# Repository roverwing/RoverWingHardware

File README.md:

Introduction
============
RoverWing is an extension board  (or "wing", following Adafruit's terminology) for Adafruit's [Feather boards](https://www.adafruit.com/feather).
This board  provides motor drivers, Inertial Motion Unit (IMU), and connection ports for servos, sonars, GPS,
and other peripherals commonly used by mobile robots. It also contains a microcontroller preloaded with firmware
to control these peripherals, which communicates with the Feather board using I2C protocol, thus freeing resources
of the Feather board for other purposes.

The RoverWing was heavily influenced by Adafruit's [CRICKIT](https://www.adafruit.com/crickit) board
(in particular, it has exact same dimensions and  mounting holes as the CRICKIT board). However, unlike CRICKIT,
it is intended for use with more powerful 6-12V motors and provides a slightly different set of peripherals.

Below is the list of key features of the RoverWing:

* Can be powered by 7-14V power source; contains a voltage regulator providing power to the Feather board

* Only uses 2 pins (SDA and SCL) of the Feather board.

* Contains on-board microcontroller, which takes care of low-level operations such as counting motor encoder pulses, using preloaded firmware

* Contains on-board 6DOF  Inertial Motion Unit (IMU),  based on ICM-42605 chip
  by Invensense, which can be used for tracking robot orientation in space

* Provides the hardware and firmware support for connecting the following external peripherals

  - Motors: two brushed DC motors, at up to 2.9A at 14V per motor
  - Quadrature encoders for each motor
  - Sonars: support for three HC-SR04 or compatible ultrasonic sensors (sonars)
  - Servos: four servos (5V)
  - Six analog inputs (3.3V)
  - NeoPixel smart LED (see note on power limit below)
  - GPS  sensor
  - one  additional I2C device

The RoverWing uses same connectors for power supply, motors, encoders, and I2C
sensors as the [REV Robotics Expansion hub](http://www.revrobotics.com/rev-31-1153)  used in [First Tech Challenge](https://www.firstinspires.org/robotics/ftc)  robotics competition, so it can
be easily used with the same motors and sensors.

   RoverWing (without the Feather), top view.

For complete documentation of RoverWing board, please visit https://roverwing-board.readthedocs.io/.

To use RoverWing board, you need to install [RoverWing library for Arduino](https://github.com/roverwing/RoverWingLibrary).

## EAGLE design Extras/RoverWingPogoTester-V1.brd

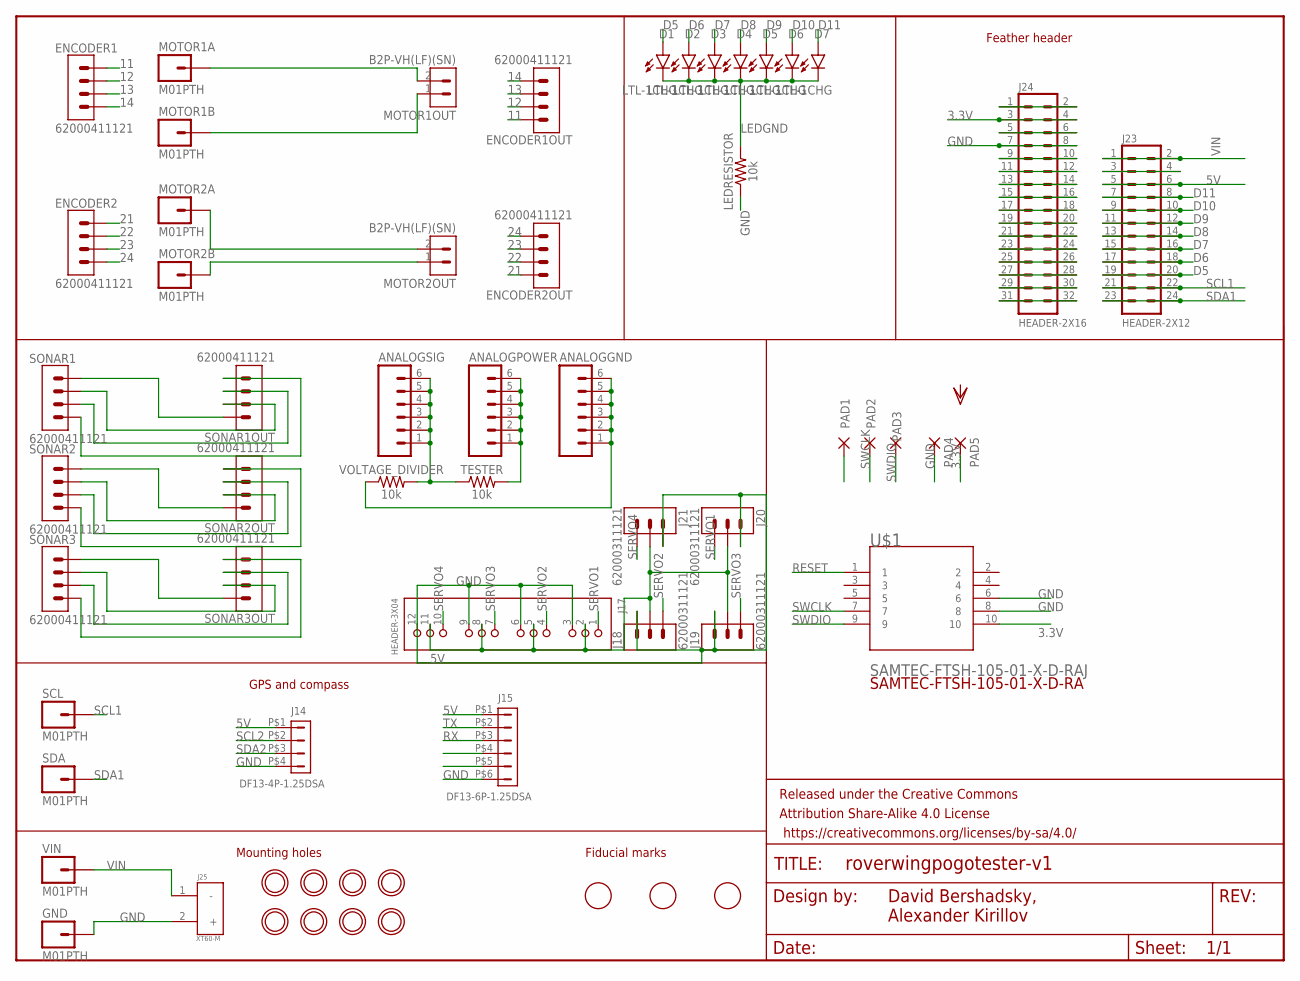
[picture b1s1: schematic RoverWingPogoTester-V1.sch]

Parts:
ANALOGGND: M06SIP; 1X06
ANALOGPOWER: M06SIP; 1X06
ANALOGSIG: M06SIP; 1X06
D1, D2, D3, D4, D5, D6, D7: LTL-1CHG; RADIAL_3MM
ENCODER1, ENCODER1OUT, ENCODER2, ENCODER2OUT: 62000411121
FRAME3: FRAME-LETTERNO_PACKAGE; DUMMY
GND: M01PTH; 1X01
J14: DF13-4P-1.25DSA
J15: DF13-6P-1.25DSA
J17: HEADER-3X04; 3X04
J18, J19, J20, J21: 62000311121
J23: HEADER-2X12; 2X12
J24: HEADER-2X16; 2X16
J25: XT60-M; AMASS_XT60-M
LEDRESISTOR: 10k; AXIAL-0.3
MOTOR1A, MOTOR1B, MOTOR2A, MOTOR2B: M01PTH; 1X01
MOTOR1OUT, MOTOR2OUT: B2P-VH(LF)(SN); HDR-02
PAD1, PAD2, PAD3, PAD4, PAD5: 2,15/1,0
SCL: M01PTH; 1X01
SDA: M01PTH; 1X01
SONAR1, SONAR1OUT, SONAR2, SONAR2OUT, SONAR3, SONAR3OUT: 62000411121
TESTER: 10k; AXIAL-0.3
U$1: SAMTEC-FTSH-105-01-X-D-RAJ; SAMTEC-FTSH-105-01-X-D-RA
U$3, U$4, U$14, U$15, U$24, U$25, U$26, U$27: MOUNTINGHOLE3.0_NPH; MOUNTINGHOLE_3.0_NPH
U$11, U$13, U$17: FIDUCIAL; FIDUCIAL_1MM
VIN: M01PTH; 1X01
VOLTAGE_DIVIDER: 10k; AXIAL-0.3

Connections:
3.3V: J24.3, J24.4, PAD5.1, U$1.10
5V: J14.P$1 (1), J15.P$1 (1), J17.2, J17.5, J17.8, J17.11, J18.2, J19.2, J20.2, J21.2, J23.5, J23.6
11: ENCODER1.1, ENCODER1OUT.1
12: ENCODER1.2, ENCODER1OUT.2
13: ENCODER1.3, ENCODER1OUT.3
14: ENCODER1.4, ENCODER1OUT.4
21: ENCODER2.1, ENCODER2OUT.1
22: ENCODER2.2, ENCODER2OUT.2
23: ENCODER2.3, ENCODER2OUT.3
24: ENCODER2.4, ENCODER2OUT.4
!RESET1: J24.1, J24.2
D5: D1.A, J23.19, J23.20
D6: D2.A, J23.17, J23.18
D7: D3.A, J23.15, J23.16
D8: D4.A, J23.13, J23.14
D9: D5.A, J23.11, J23.12
D10: D6.A, J23.9, J23.10
D11: D7.A, J23.7, J23.8
GND: GND.1, J14.P$4 (4), J15.P$6 (6), J17.3, J17.6, J17.9, J17.12, J18.1, J19.1, J20.1, J21.1, J24.7, J24.8, J25.2 (+), LEDRESISTOR.P$1 (1), PAD4.1, U$1.6, U$1.8
LEDGND: D1.C, D2.C, D3.C, D4.C, D5.C, D6.C, D7.C, LEDRESISTOR.P$2 (2)
unnamed: MOTOR1A.1, MOTOR1OUT.2
unnamed: MOTOR1B.1, MOTOR1OUT.1
unnamed: MOTOR2A.1, MOTOR2OUT.2
unnamed: MOTOR2B.1, MOTOR2OUT.1
unnamed: SONAR1.4, SONAR1OUT.4
unnamed: SONAR1.3, SONAR1OUT.3
unnamed: SONAR1.2, SONAR1OUT.2
unnamed: ANALOGPOWER.1, ANALOGPOWER.2, ANALOGPOWER.3, ANALOGPOWER.4, ANALOGPOWER.5, ANALOGPOWER.6, TESTER.P$2 (2)
unnamed: SONAR1.1, SONAR1OUT.1
unnamed: SONAR2.4, SONAR2OUT.4
unnamed: SONAR2.3, SONAR2OUT.3
unnamed: SONAR2.2, SONAR2OUT.2
unnamed: SONAR2.1, SONAR2OUT.1
unnamed: SONAR3.4, SONAR3OUT.4
unnamed: SONAR3.3, SONAR3OUT.3
unnamed: SONAR3.2, SONAR3OUT.2
unnamed: SONAR3.1, SONAR3OUT.1
unnamed: ANALOGSIG.1, ANALOGSIG.2, ANALOGSIG.3, ANALOGSIG.4, ANALOGSIG.5, ANALOGSIG.6, TESTER.P$1 (1), VOLTAGE_DIVIDER.P$2 (2)
unnamed: ANALOGGND.1, ANALOGGND.2, ANALOGGND.3, ANALOGGND.4, ANALOGGND.5, ANALOGGND.6, VOLTAGE_DIVIDER.P$1 (1)
unnamed: J23.3, J23.4
unnamed: J24.5, J24.6
unnamed: J24.9, J24.10
unnamed: J24.11, J24.12
unnamed: J24.13, J24.14
unnamed: J24.15, J24.16
unnamed: J24.17, J24.18
unnamed: J24.19, J24.20
unnamed: J24.21, J24.22
unnamed: J24.23, J24.24
unnamed: J24.25, J24.26
unnamed: J24.27, J24.28
unnamed: J24.29, J24.30
unnamed: J24.31, J24.32
RESET: PAD1.1, U$1.1
RX: J15.P$3 (3)
SCL1: J23.21, J23.22, SCL.1
SCL2: J14.P$2 (2)
SDA1: J23.23, J23.24, SDA.1
SDA2: J14.P$3 (3)
SERVO1: J17.1, J20.3
SERVO2: J17.4, J18.3
SERVO3: J17.7, J19.3
SERVO4: J17.10, J21.3
SWCLK: PAD2.1, U$1.7
SWDIO: PAD3.1, U$1.9
TX: J15.P$2 (2)
VIN: J23.1, J23.2, J25.1 (-), VIN.1

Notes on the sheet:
David Bershadsky, Alexander Kirillov
Feather header
GPS and compass
Mounting holes
Fiducial marks

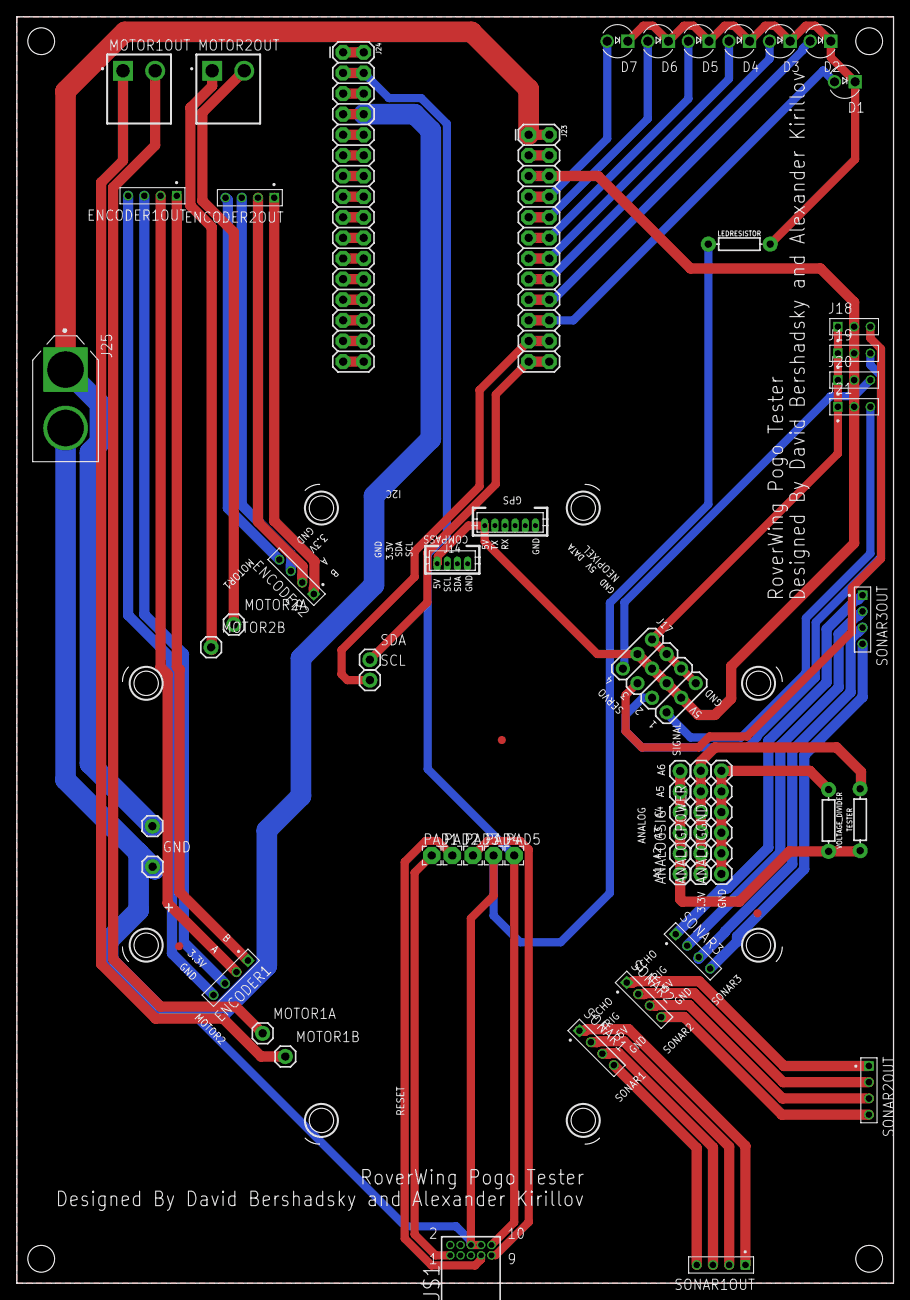
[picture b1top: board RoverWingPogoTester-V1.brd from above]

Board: 2 copper layers, 108.0 x 156.0 mm, 61 parts (0 on the bottom side), 63 nets.

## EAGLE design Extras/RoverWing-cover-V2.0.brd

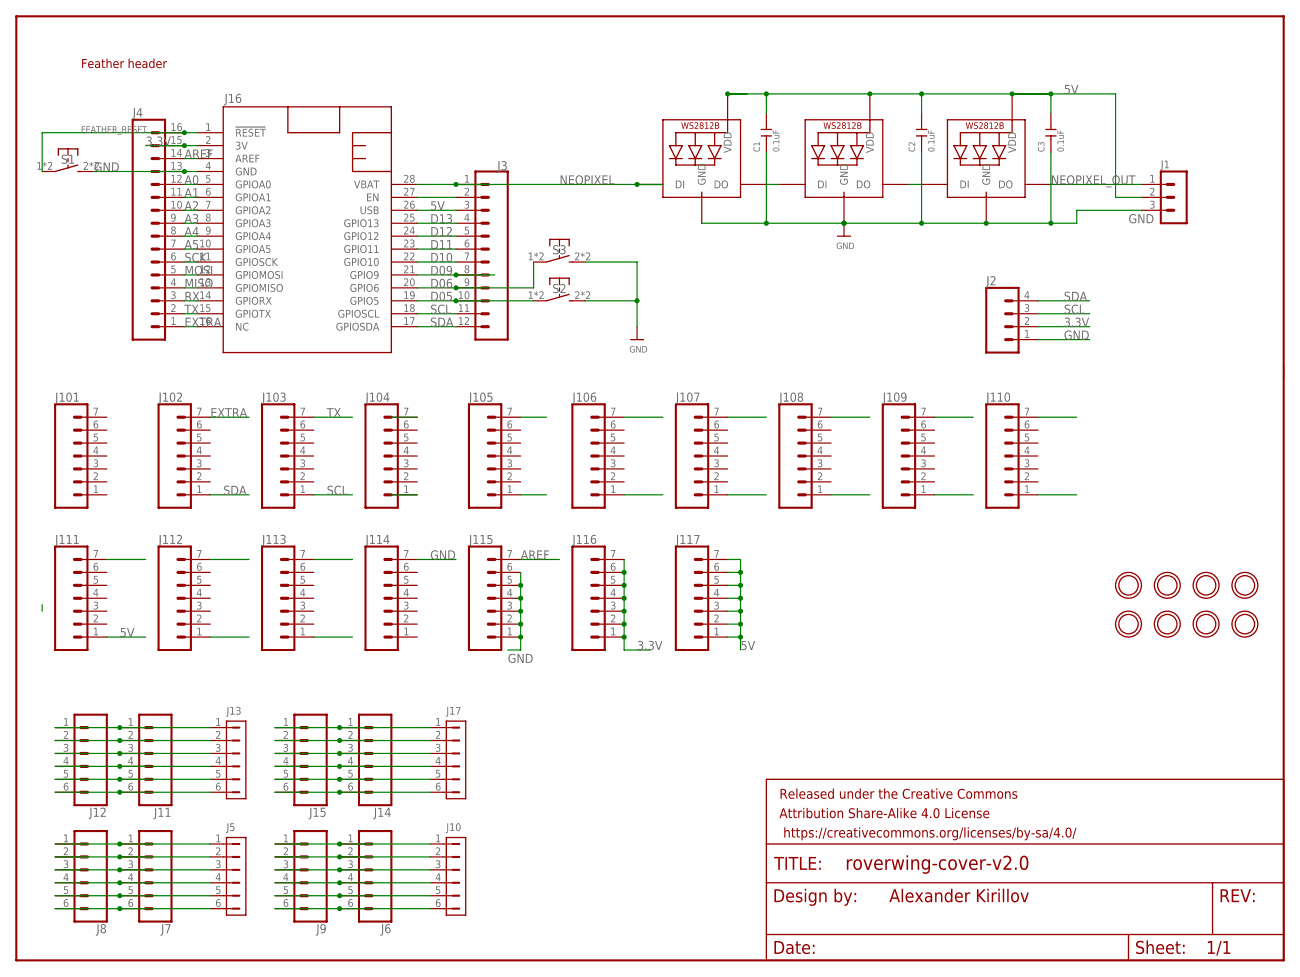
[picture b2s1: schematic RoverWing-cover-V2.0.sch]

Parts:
C1, C2, C3: 0.1uF; C0805; MPN 04025C104KAT2A
FRAME2: FRAME-LETTERNO_PACKAGE; DUMMY
J1: HEADER-PH-3PSIDEENTRY; S3B-PH-K; MPN S3B-PH-K-S (LF)(SN)
J2: CONN_04; 1X04
J3: CONN_12NO_SILK; 1X12_NO_SILK
J4: CONN_161X16_NO_SILK; 1X16_NO_SILK
J5, J10, J13, J17: HEADER-PH-6PSIDEENTRY; S6B-PH-K
J6, J7, J8, J9, J11, J12, J14, J15: CONN_06NO_SILK_NO_POP; 1X06_NO_SILK
J16: FEATHERWING_NODIM; FEATHERWING_DIM
J101, J102, J103, J104, J105, J106, J107, J108, J109, J110, J111, J112, J113, J114, J115, J116, J117: CONN_07NO_SILK; 1X07_NO_SILK
LED1, LED2, LED3: WS2812B3535; LED3535; MPN 2659
S1, S2, S3: SW-TACTILE-4.5X4.5_SMD; TL3305; MPN TL3305AF160QG
U$3, U$4, U$14, U$15, U$24, U$25, U$26, U$27: MOUNTINGHOLE3.0_NPH; MOUNTINGHOLE_3.0_NPH

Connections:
3.3V: J2.2, J4.15, J16.2 (3V), J116.1, J116.2, J116.3, J116.4, J116.5, J116.6, J116.7
5V: C1.2, C2.2, C3.2, J1.2, J3.3, J16.26 (USB), J111.1, J117.1, J117.2, J117.3, J117.4, J117.5, J117.6, J117.7, LED1.3 (VDD), LED2.3 (VDD), LED3.3 (VDD)
A0: J4.12, J16.5 (GPIOA0), J113.7
A1: J4.11, J16.6 (GPIOA1), J112.7
A2: J4.10, J16.7 (GPIOA2), J111.7
A3: J4.9, J16.8 (GPIOA3), J110.7
A4: J4.8, J16.9 (GPIOA4), J109.7
A5: J4.7, J16.10 (GPIOA5), J108.7
AREF: J4.14, J16.3 (AREF), J115.7
D05: J3.10, J16.19 (GPIO5), J104.1, S2.1, S2.4 (P1)
D06: J3.9, J16.20 (GPIO6), J105.1, S3.1, S3.4 (P1)
D09: J3.8, J16.21 (GPIO9), J106.1
D10: J3.7, J16.22 (GPIO10), J107.1
D11: J3.6, J16.23 (GPIO11), J108.1
D12: J3.5, J16.24 (GPIO12), J109.1
D13: J3.4, J16.25 (GPIO13), J110.1
EXTRA: J4.1, J16.16 (NC), J102.7
FEATHER_RESET: J4.16, J16.1 (!RESET), S1.1, S1.4 (P1)
GND: C1.1, C2.1, C3.1, J1.3, J2.1, J4.13, J16.4 (GND), J114.7, J115.1, J115.2, J115.3, J115.4, J115.5, J115.6, LED1.1 (GND), LED2.1 (GND), LED3.1 (GND), S1.2 (S1), S1.3 (S1), S2.2 (S1), S2.3 (S1), S3.2 (S1), S3.3 (S1)
MISO: J4.4, J16.13 (GPIOMISO), J105.7
MOSI: J4.5, J16.12 (GPIOMOSI), J106.7
unnamed: LED2.4 (DO), LED3.2 (DI)
unnamed: J5.1, J7.1, J8.1
unnamed: LED1.4 (DO), LED2.2 (DI)
unnamed: J5.2, J7.2, J8.2
unnamed: J5.3, J7.3, J8.3
unnamed: J5.4, J7.4, J8.4
unnamed: J5.5, J7.5, J8.5
unnamed: J5.6, J7.6, J8.6
unnamed: J6.1, J9.1, J10.1
unnamed: J6.2, J9.2, J10.2
unnamed: J6.3, J9.3, J10.3
unnamed: J6.4, J9.4, J10.4
unnamed: J6.5, J9.5, J10.5
unnamed: J6.6, J9.6, J10.6
unnamed: J11.1, J12.1, J13.1
unnamed: J11.2, J12.2, J13.2
unnamed: J11.3, J12.3, J13.3
unnamed: J11.4, J12.4, J13.4
unnamed: J11.5, J12.5, J13.5
unnamed: J11.6, J12.6, J13.6
unnamed: J14.1, J15.1, J17.1
unnamed: J14.2, J15.2, J17.2
unnamed: J14.3, J15.3, J17.3
unnamed: J14.4, J15.4, J17.4
unnamed: J14.5, J15.5, J17.5
unnamed: J14.6, J15.6, J17.6
unnamed: J3.2, J16.27 (EN), J112.1
NEOPIXEL: J3.1, J16.28 (VBAT), LED1.2 (DI)
NEOPIXEL_OUT: J1.1, LED3.4 (DO)
RX: J4.3, J16.14 (GPIORX), J104.7
SCK: J4.6, J16.11 (GPIOSCK), J107.7
SCL: J2.3, J3.11, J16.18 (GPIOSCL), J103.1
SDA: J2.4, J3.12, J16.17 (GPIOSDA), J102.1
TX: J4.2, J16.15 (GPIOTX), J103.7

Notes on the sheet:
Alexander Kirillov
Feather header

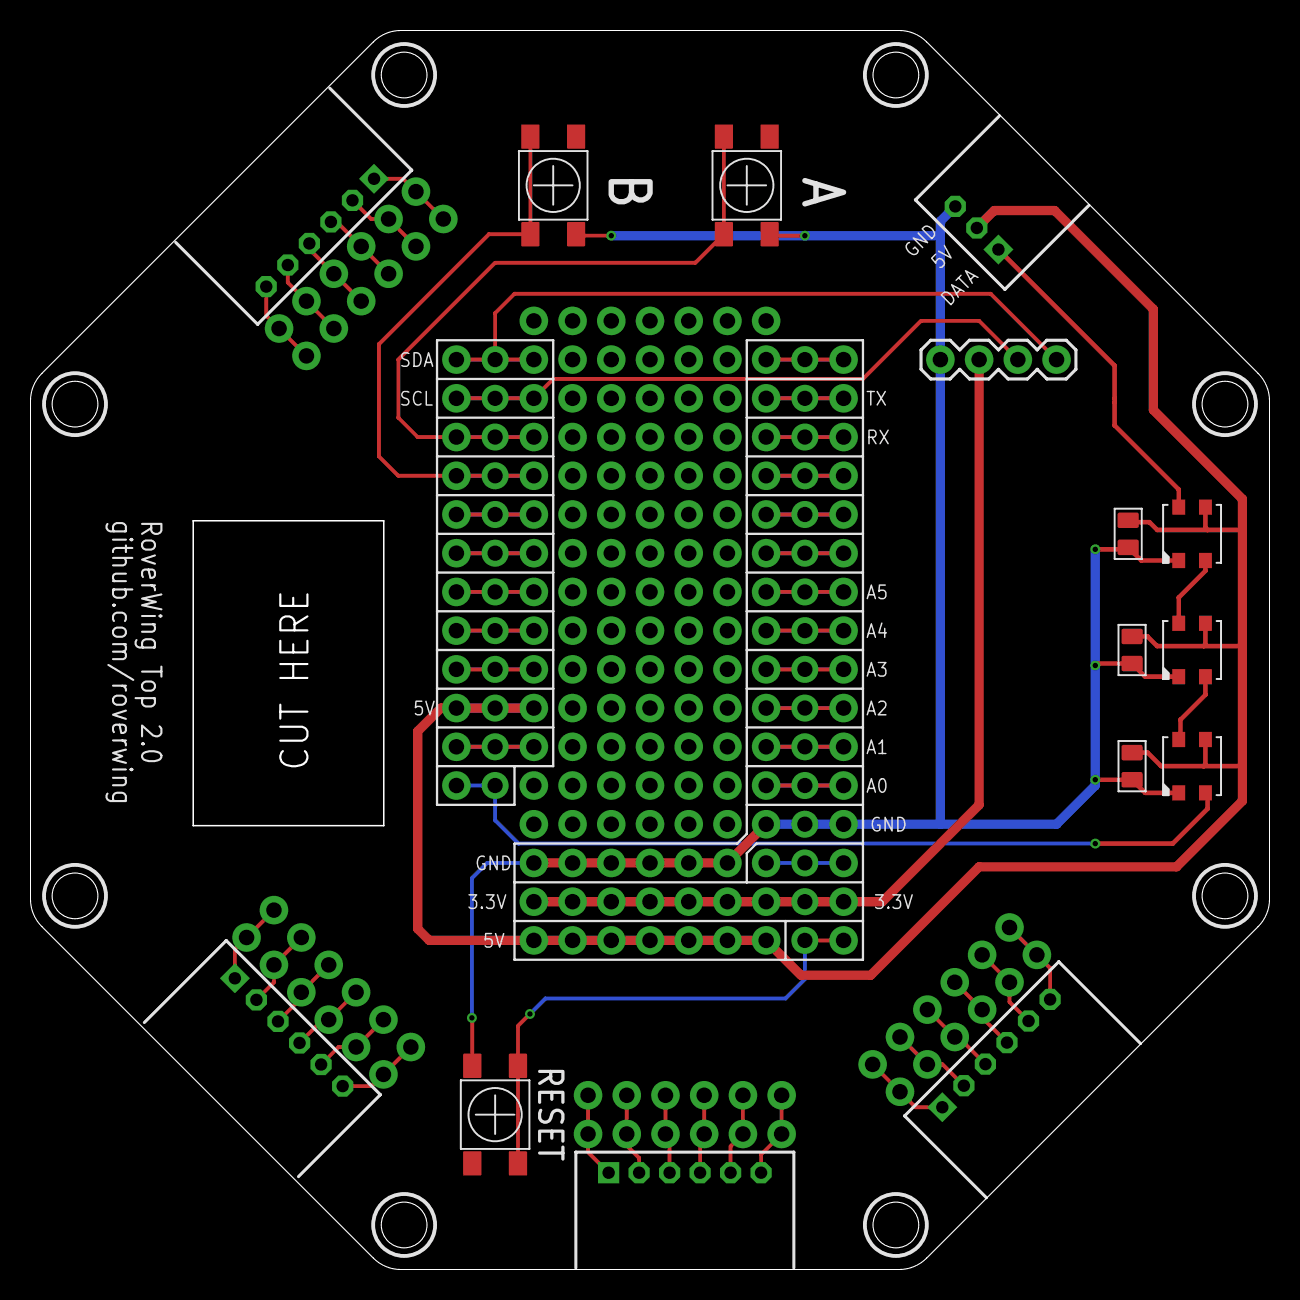
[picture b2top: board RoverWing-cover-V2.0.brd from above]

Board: 2 copper layers, 81.3 x 81.3 mm, 52 parts (0 on the bottom side), 55 nets.

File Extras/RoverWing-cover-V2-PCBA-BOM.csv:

Order list for /Users/davidbershadsky/Documents/Roverwing/RoverWingHardware/Extras/RoverWing-cover-V2.0.sch
Exported from EAGLE with DesignLink

Quantity	Value	Package	Order code	Manufacturer	Manuf. Code	Availability	Price (from)	Description
3	0.1uF	C0805	96Y8186	AVX	04025C104KAT2A	9540	0.131	AVX - 04025C104KAT2A - SMD Multilayer Ceramic Capacitor, 0.1 &#181;F, 50 V, 0402 [1005 Metric], &#177; 10%, X7R
1	FRAME-LETTERNO_PACKAGE	DUMMY	unknown					
1	HEADER-PH-3PSIDEENTRY	S3B-PH-K	38K8070	JST (JAPAN SOLDERLESS TERMINALS)	S3B-PH-K-S (LF)(SN)	7505	0.075	JST (JAPAN SOLDERLESS TERMINALS) - S3B-PH-K-S (LF)(SN) - Pin Header, Wire-to-Board, 2 mm, 1 Rows, 3 Contacts, Through Hole, PH Series
1		1X04	unknown					
1		1X12_NO_SILK	unknown					
1		1X16_NO_SILK	unknown					
4	HEADER-PH-6PSIDEENTRY	S6B-PH-K	unknown					
8		1X06_NO_SILK	unknown					
1	FEATHERWING_NODIM	FEATHERWING_DIM	unknown					
17		1X07_NO_SILK	unknown					
3		LED3535	77Y5297	ADAFRUIT	2659	0	49.5	ADAFRUIT - 2659 - NEOPIXEL MINI 3535 RGB LEDS W/ INTEGRATED DRIVER CHIP - WHITE - PACK OF 10
3	SW-TACTILE-4.5X4.5_SMD	TL3305	84Y2774	E-SWITCH	TL3305AF160QG	2716	0.126	E-SWITCH - TL3305AF160QG - Tactile Switch, Ultraminiature, TL3305 Series, Top Actuated, Surface Mount, Round Button, 160 gf
8	MOUNTINGHOLE3.0_NPH	MOUNTINGHOLE_3.0_NPH	unknown

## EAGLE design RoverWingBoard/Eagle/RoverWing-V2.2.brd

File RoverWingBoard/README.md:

# Hardware
This directory contains hardware design files: Eagle schematics and board files, bill of materials, etc.

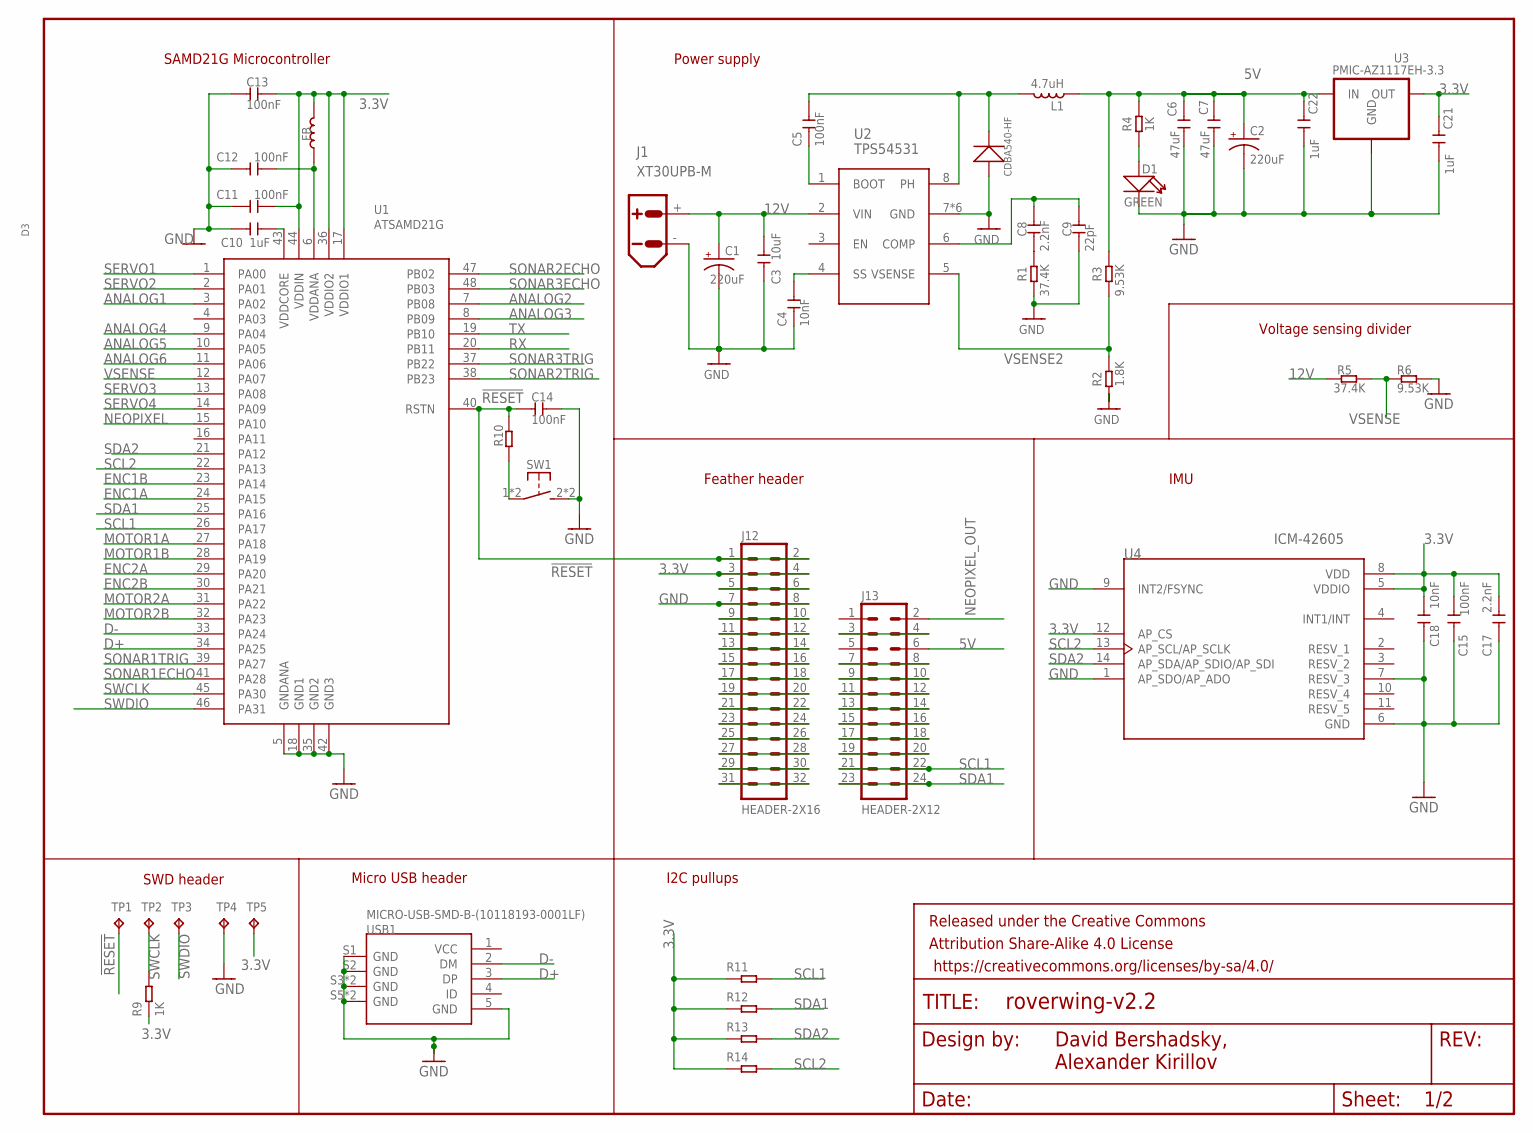
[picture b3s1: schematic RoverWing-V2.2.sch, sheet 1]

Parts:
C1, C2: 220uF; CAP-8X10.5
C3: 10uF; 0805
C4, C18: 10nF; 0603
C5, C11, C12, C13, C14, C15: 100nF; 0603
C6, C7: 47uF; 1206
C8, C17: 2.2nF; 0603
C9: 22pF; 0603
C10, C21, C22: 1uF; 0603
D1: GREEN; LED-0805
D3: CDBA540-HF; SMA-DO214AC
FB: 330R-1500MA; 0805
FRAME2: FRAME-LETTERNO_PACKAGE; DUMMY
J1: XT30UPB-M
J12: HEADER-2X16; 2X16
J13: HEADER-2X12; 2X12
L1: 4.7uH; IND_TDK_7.1X6.5
R1, R5: 37.4K; 0603
R2, R11, R12, R13, R14: 1.8K; 0603
R3, R6: 9.53K; 0603
R4, R9, R10: 1K; 0603
SW1: SW-TACTILE-4.5X4.5_SMD; TL3305
TP1, TP2, TP3, TP4, TP5: TPTP15R; TP15R
U1: ATSAMD21G; TQFP-48-EDITED
U2: TPS54531; HSOP8
U3: PMIC-AZ1117EH-3.3; SOT223
U4: ICM-42605; PQFN50P300X250X97-14N
USB1: MICRO-USB-SMD-B-(10118193-0001LF); MICRO-USB5+6P-SMD-0.65-B

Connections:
3.3V: C11.2, C13.2, C15.2, C17.2, C18.1, C21.2, FB.2, J12.3, J12.4, R9.1, R11.1, R12.1, R13.1, R14.1, TP5.TP, U1.17 (VDDIO1), U1.36 (VDDIO2), U1.44 (VDDIN), U3.2 (OUT), U3.4 (OUT), U4.5 (VDDIO), U4.8 (VDD), U4.12 (AP_CS); also elsewhere on the board
5V: C2.+, C6.2, C7.2, C22.2, J13.6, L1.1, R3.2, R4.2, U3.3 (IN); also elsewhere on the board
12V: C1.+, C3.2, J1.+, R5.2, U2.2 (VIN); also elsewhere on the board
!RESET: C14.1, J12.1, J12.2, R10.2, TP1.TP, U1.40 (RSTN)
ANALOG1: U1.3 (PA02); also elsewhere on the board
ANALOG2: U1.7 (PB08); also elsewhere on the board
ANALOG3: U1.8 (PB09); also elsewhere on the board
ANALOG4: U1.9 (PA04); also elsewhere on the board
ANALOG5: U1.10 (PA05); also elsewhere on the board
ANALOG6: U1.11 (PA06); also elsewhere on the board
BOOT: C5.1, U2.1 (BOOT)
D+: U1.34 (PA25), USB1.3 (DP)
D-: U1.33 (PA24), USB1.2 (DM)
ENC1A: U1.24 (PA15); also elsewhere on the board
ENC1B: U1.23 (PA14); also elsewhere on the board
ENC2A: U1.29 (PA20); also elsewhere on the board
ENC2B: U1.30 (PA21); also elsewhere on the board
GND: C1.-, C2.-, C3.1, C4.1, C6.1, C7.1, C9.1, C10.1, C11.1, C12.1, C13.1, C14.2, C15.1, C17.1, C18.2, C21.1, C22.1, D1.-, D3.A (+), J1.-, J12.7, J12.8, R1.1, R2.1, R6.2, SW1.2 (S1), SW1.3 (S1), TP4.TP, U1.5 (GNDANA), U1.18 (GND1), U1.35 (GND2), U1.42 (GND3), U2.7 (GND), U2.GND, U2.P$1 (GND), U2.P$2 (GND), U2.P$3 (GND), U2.P$4 (GND), U3.1 (GND), U4.1 (AP_SDO/AP_ADO), U4.6 (GND), U4.7 (RESV_3), U4.9 (INT2/FSYNC), USB1.5 (GND), USB1.S1 (GND), USB1.S2 (GND), USB1.S3 (GND), USB1.S4 (GND), USB1.S5 (GND), USB1.S6 (GND); also elsewhere on the board
MOTOR1A: U1.27 (PA18); also elsewhere on the board
MOTOR1B: U1.28 (PA19); also elsewhere on the board
MOTOR2A: U1.31 (PA22); also elsewhere on the board
MOTOR2B: U1.32 (PA23); also elsewhere on the board
unnamed: J13.3, J13.4
unnamed: J13.7, J13.8
unnamed: R10.1, SW1.1, SW1.4 (P1)
unnamed: J13.9, J13.10
unnamed: C10.2, U1.43 (VDDCORE)
unnamed: J13.11, J13.12
unnamed: D1.+, R4.1
unnamed: J13.15, J13.16
unnamed: J13.13, J13.14
unnamed: C5.2, D3.K (-), L1.2, U2.8 (PH)
unnamed: C4.2, U2.4 (SS)
unnamed: J12.5, J12.6
unnamed: C8.1, R1.2
unnamed: C8.2, C9.2, U2.6 (COMP)
unnamed: J13.17, J13.18
unnamed: J13.19, J13.20
unnamed: J12.9, J12.10
unnamed: J12.11, J12.12
unnamed: J12.13, J12.14
unnamed: J12.15, J12.16
unnamed: J12.17, J12.18
unnamed: J12.19, J12.20
unnamed: J12.21, J12.22
unnamed: J12.23, J12.24
unnamed: J12.25, J12.26
unnamed: J12.27, J12.28
unnamed: J12.29, J12.30
unnamed: J12.31, J12.32
NEOPIXEL: U1.15 (PA10); also elsewhere on the board
NEOPIXEL_OUT: J13.2; also elsewhere on the board
RX: U1.20 (PB11); also elsewhere on the board
SCL1: J13.21, J13.22, R11.2, U1.26 (PA17); also elsewhere on the board
SCL2: R14.2, U1.22 (PA13), U4.13 (AP_SCL/AP_SCLK); also elsewhere on the board
SDA1: J13.23, J13.24, R12.2, U1.25 (PA16); also elsewhere on the board
SDA2: R13.2, U1.21 (PA12), U4.14 (AP_SDA/AP_SDIO/AP_SDI); also elsewhere on the board
SERVO1: U1.1 (PA00); also elsewhere on the board
SERVO2: U1.2 (PA01); also elsewhere on the board
SERVO3: U1.13 (PA08); also elsewhere on the board
SERVO4: U1.14 (PA09); also elsewhere on the board
SONAR1ECHO: U1.41 (PA28); also elsewhere on the board
SONAR1TRIG: U1.39 (PA27); also elsewhere on the board
SONAR2ECHO: U1.47 (PB02); also elsewhere on the board
SONAR2TRIG: U1.38 (PB23); also elsewhere on the board
SONAR3ECHO: U1.48 (PB03); also elsewhere on the board
SONAR3TRIG: U1.37 (PB22); also elsewhere on the board
SWCLK: R9.2, TP2.TP, U1.45 (PA30)
SWDIO: TP3.TP, U1.46 (PA31)
TX: U1.19 (PB10); also elsewhere on the board
VDDANA: C12.2, FB.1, U1.6 (VDDANA)
VSENSE: R5.1, R6.1, U1.12 (PA07)
VSENSE2: R2.2, R3.1, U2.5 (VSENSE)

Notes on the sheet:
SWD header
David Bershadsky, Alexander Kirillov
SAMD21G Microcontroller
Micro USB header
Power supply
Feather header
IMU
Voltage sensing divider
I2C pullups

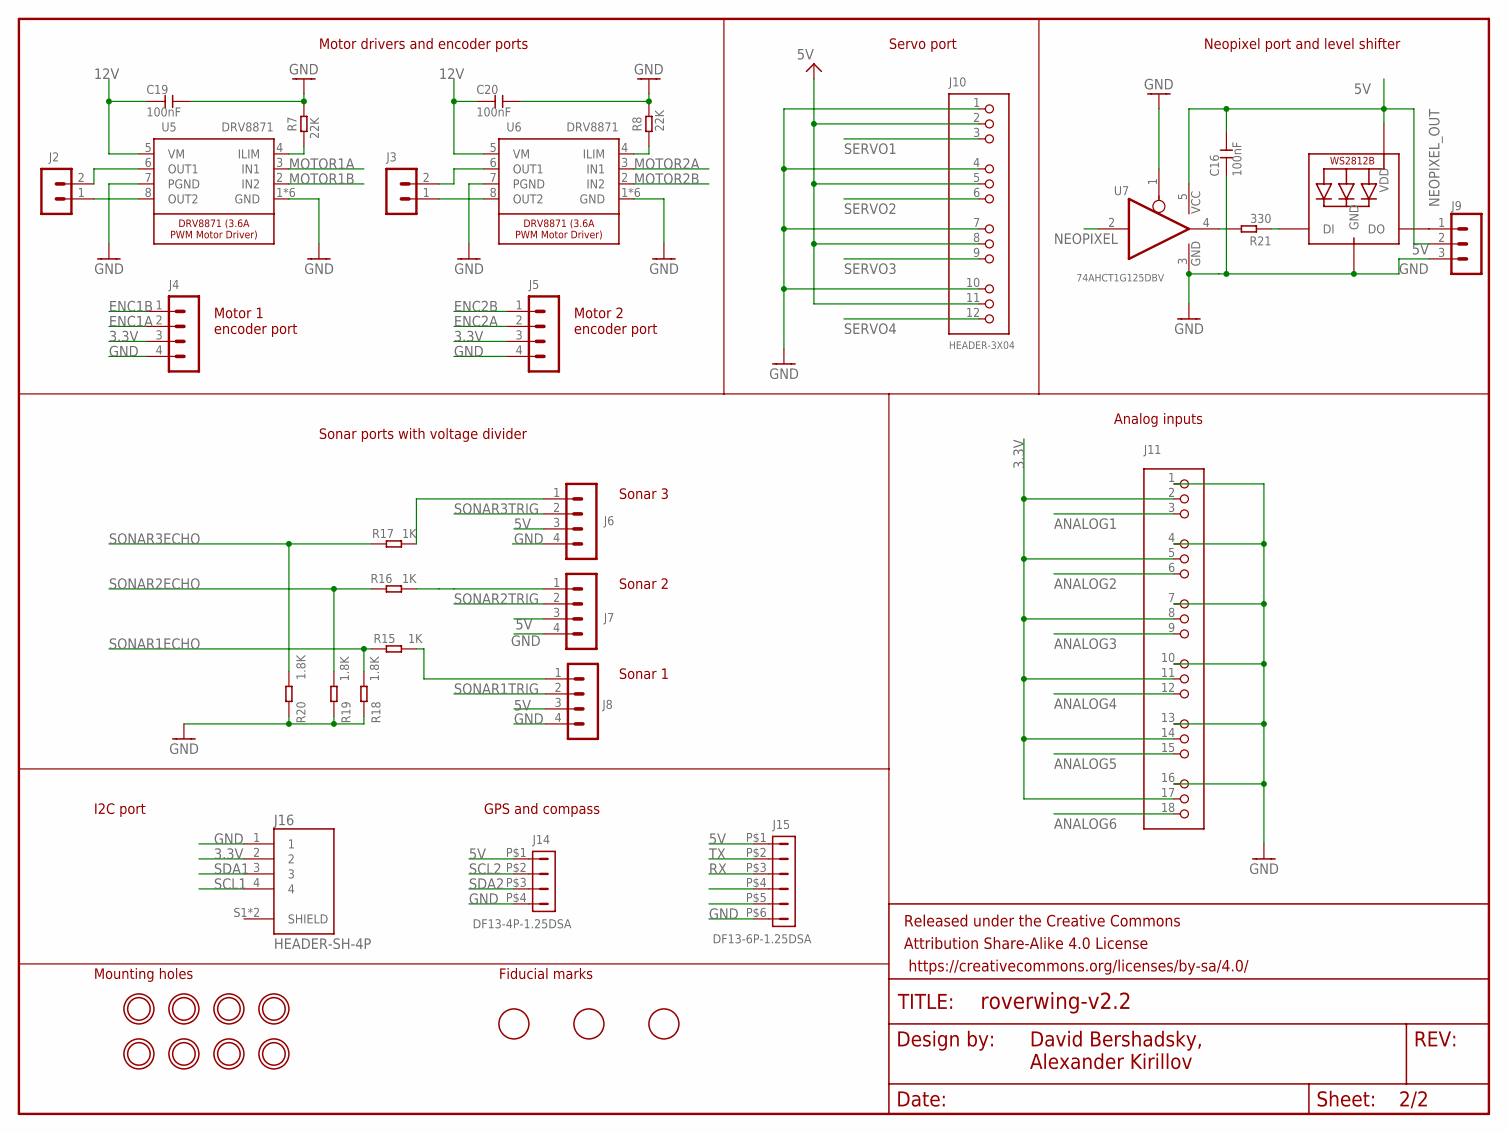
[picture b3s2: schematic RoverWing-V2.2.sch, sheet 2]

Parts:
C16, C19, C20: 100nF; 0603
D2: WS2812B3535; LED3535
FRAME1: FRAME-LETTERNO_PACKAGE; DUMMY
J2, J3: HEADER-VH; B2P-VH
J4, J5, J6, J7, J8: HEADER-PH-4P; B4B-PH-K
J9: HEADER-PH-3P; B3B-PH-K
J10: HEADER-3X04; 3X04
J11: HEADER-3X06ANGLE; 3X06
J14: DF13-4P-1.25DSA
J15: DF13-6P-1.25DSA
J16: HEADER-SH-4P; CONN_BM04B-SRSS-TB(LF)(SN)
R7, R8: 22K; 0603
R15, R16, R17: 1K; 0603
R18, R19, R20: 1.8K; 0603
R21: 330; 0603
U5, U6: DRV8871; HSOP8
U7: 74AHCT1G125DBV; SOT23-5
U$3, U$4, U$14, U$15, U$24, U$25, U$26, U$27: MOUNTINGHOLE3.0_NPH; MOUNTINGHOLE_3.0_NPH
U$11, U$13, U$17: FIDUCIAL; FIDUCIAL_1MM

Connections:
3.3V: J4.3, J5.3, J11.2, J11.5, J11.8, J11.11, J11.14, J11.17, J16.2; also elsewhere on the board
5V: C16.2, D2.3 (VDD), J6.3, J7.3, J8.3, J9.2, J10.2, J10.5, J10.8, J10.11, J14.P$1 (1), J15.P$1 (1), U7.5 (VCC); also elsewhere on the board
12V: C19.1, C20.1, U5.5 (VM), U6.5 (VM); also elsewhere on the board
ANALOG1: J11.3; also elsewhere on the board
ANALOG2: J11.6; also elsewhere on the board
ANALOG3: J11.9; also elsewhere on the board
ANALOG4: J11.12; also elsewhere on the board
ANALOG5: J11.15; also elsewhere on the board
ANALOG6: J11.18; also elsewhere on the board
ENC1A: J4.2; also elsewhere on the board
ENC1B: J4.1; also elsewhere on the board
ENC2A: J5.2; also elsewhere on the board
ENC2B: J5.1; also elsewhere on the board
GND: C16.1, C19.2, C20.2, D2.1 (GND), J4.4, J5.4, J6.4, J7.4, J8.4, J9.3, J10.1, J10.4, J10.7, J10.10, J11.1, J11.4, J11.7, J11.10, J11.13, J11.16, J14.P$4 (4), J15.P$6 (6), J16.1, R7.2, R8.2, R18.2, R19.2, R20.2, U5.1 (GND), U5.7 (PGND), U5.GND, U5.P$1 (GND), U5.P$2 (GND), U5.P$3 (GND), U5.P$4 (GND), U6.1 (GND), U6.7 (PGND), U6.GND, U6.P$1 (GND), U6.P$2 (GND), U6.P$3 (GND), U6.P$4 (GND), U7.1 (OE), U7.3 (GND); also elsewhere on the board
MOTOR1A: U5.3 (IN1); also elsewhere on the board
MOTOR1B: U5.2 (IN2); also elsewhere on the board
MOTOR2A: U6.3 (IN1); also elsewhere on the board
MOTOR2B: U6.2 (IN2); also elsewhere on the board
unnamed: J3.1, U6.8 (OUT2)
unnamed: J3.2, U6.6 (OUT1)
unnamed: J2.1, U5.8 (OUT2)
unnamed: R21.2, U7.4 (O)
unnamed: D2.2 (DI), R21.1
unnamed: J8.1, R15.1
unnamed: J6.1, R17.1
unnamed: J2.2, U5.6 (OUT1)
unnamed: R7.1, U5.4 (ILIM)
unnamed: R8.1, U6.4 (ILIM)
unnamed: J7.1, R16.1
NEOPIXEL: U7.2 (I); also elsewhere on the board
NEOPIXEL_OUT: D2.4 (DO), J9.1; also elsewhere on the board
RX: J15.P$3 (3); also elsewhere on the board
SCL1: J16.4; also elsewhere on the board
SCL2: J14.P$2 (2); also elsewhere on the board
SDA1: J16.3; also elsewhere on the board
SDA2: J14.P$3 (3); also elsewhere on the board
SERVO1: J10.3; also elsewhere on the board
SERVO2: J10.6; also elsewhere on the board
SERVO3: J10.9; also elsewhere on the board
SERVO4: J10.12; also elsewhere on the board
SONAR1ECHO: R15.2, R18.1; also elsewhere on the board
SONAR1TRIG: J8.2; also elsewhere on the board
SONAR2ECHO: R16.2, R19.1; also elsewhere on the board
SONAR2TRIG: J7.2; also elsewhere on the board
SONAR3ECHO: R17.2, R20.1; also elsewhere on the board
SONAR3TRIG: J6.2; also elsewhere on the board
TX: J15.P$2 (2); also elsewhere on the board

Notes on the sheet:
Motor drivers and encoder ports
Motor 2 encoder port
Motor 1 encoder port
Sonar ports with voltage divider
Analog inputs
Neopixel port and level shifter
Servo port
Sonar 3
Sonar 2
Sonar 1
Mounting holes
Fiducial marks
I2C port
GPS and compass
David Bershadsky, Alexander Kirillov

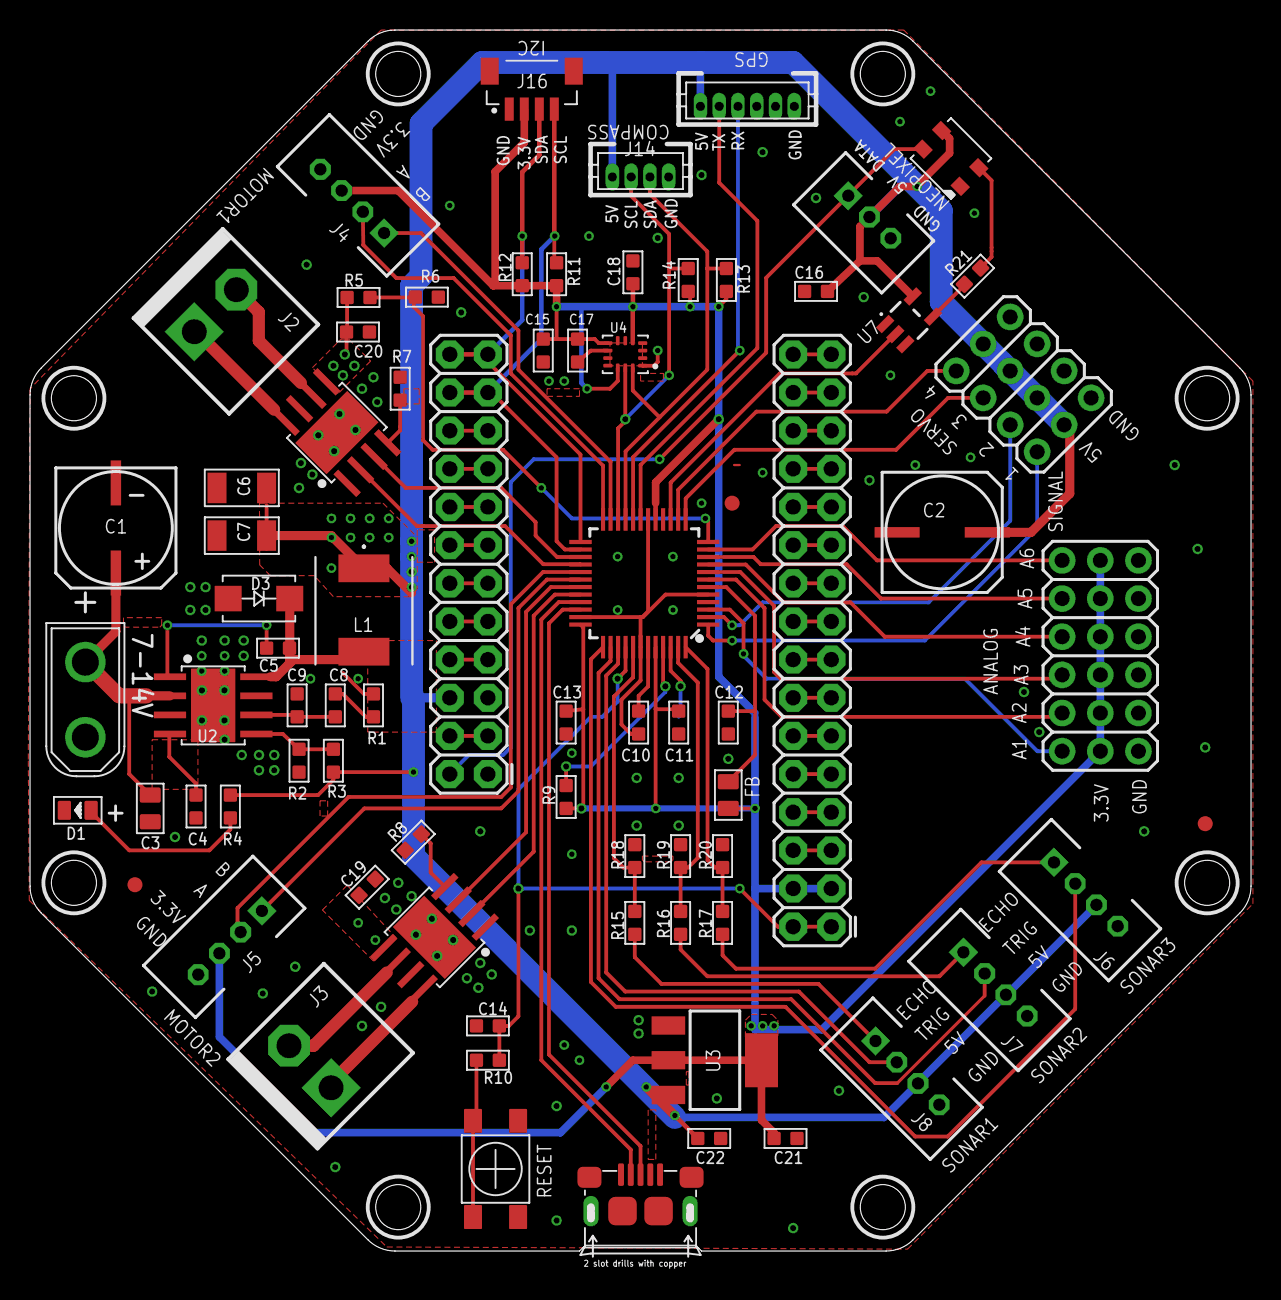
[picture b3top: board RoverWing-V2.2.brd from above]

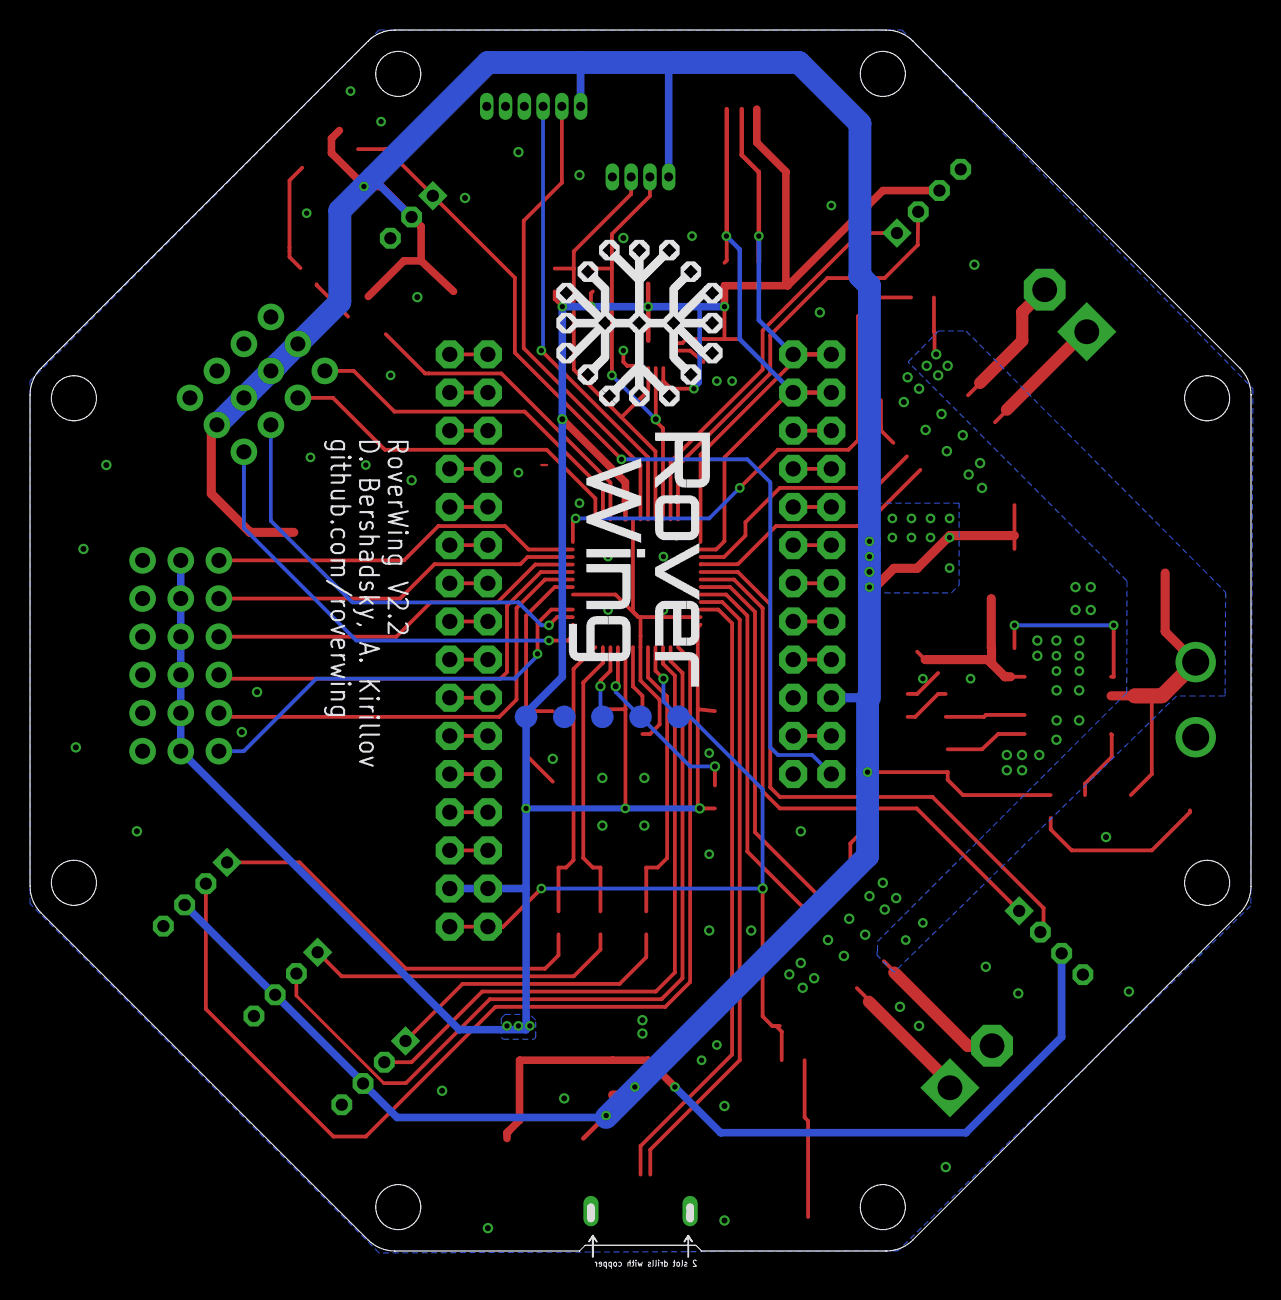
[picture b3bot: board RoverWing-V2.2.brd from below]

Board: 2 copper layers, 81.3 x 81.3 mm, 91 parts (5 on the bottom side), 84 nets.

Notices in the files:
parts and their libraries:
SparkFun-Aesthetics: Licensing: Creative Commons ShareAlike 4.0 International - https://creativecommons.org/licenses/by-sa/4.0
SparkFun-Aesthetics: Released under the Creative Commons Attribution Share-Alike 4.0 License
SparkFun-Aesthetics: https://creativecommons.org/licenses/by-sa/4.0
